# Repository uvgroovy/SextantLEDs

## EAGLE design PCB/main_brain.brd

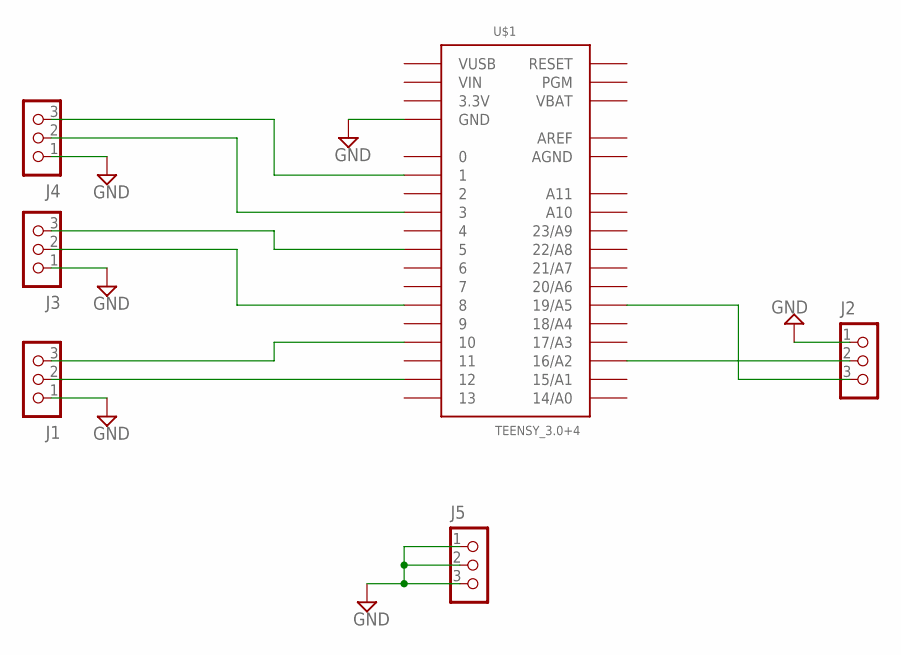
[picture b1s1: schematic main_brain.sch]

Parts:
J1, J2, J3, J4, J5: CON_TERMINAL_BLOCK_03-5MM; TERMINAL_BLOCK_3P_5
U$1: TEENSY_3.0+4

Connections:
3.3V: U$1.3.3V, U$1.3.3V1 (3.3V)
AGND: U$1.AGND
AREF: U$1.AREF
GND: J1.1, J2.1, J3.1, J4.1, J5.1, J5.2, J5.3, U$1.GND, U$1.GND1 (GND)
unnamed: J1.2, U$1.12
unnamed: J4.2, U$1.3
unnamed: J4.3, U$1.1
unnamed: J3.3, U$1.5
unnamed: J3.2, U$1.8
unnamed: J1.3, U$1.10
unnamed: J2.2, U$1.16/A2
unnamed: J2.3, U$1.19/A5
VBAT: U$1.VBAT
VIN: U$1.VIN
VUSB: U$1.VUSB

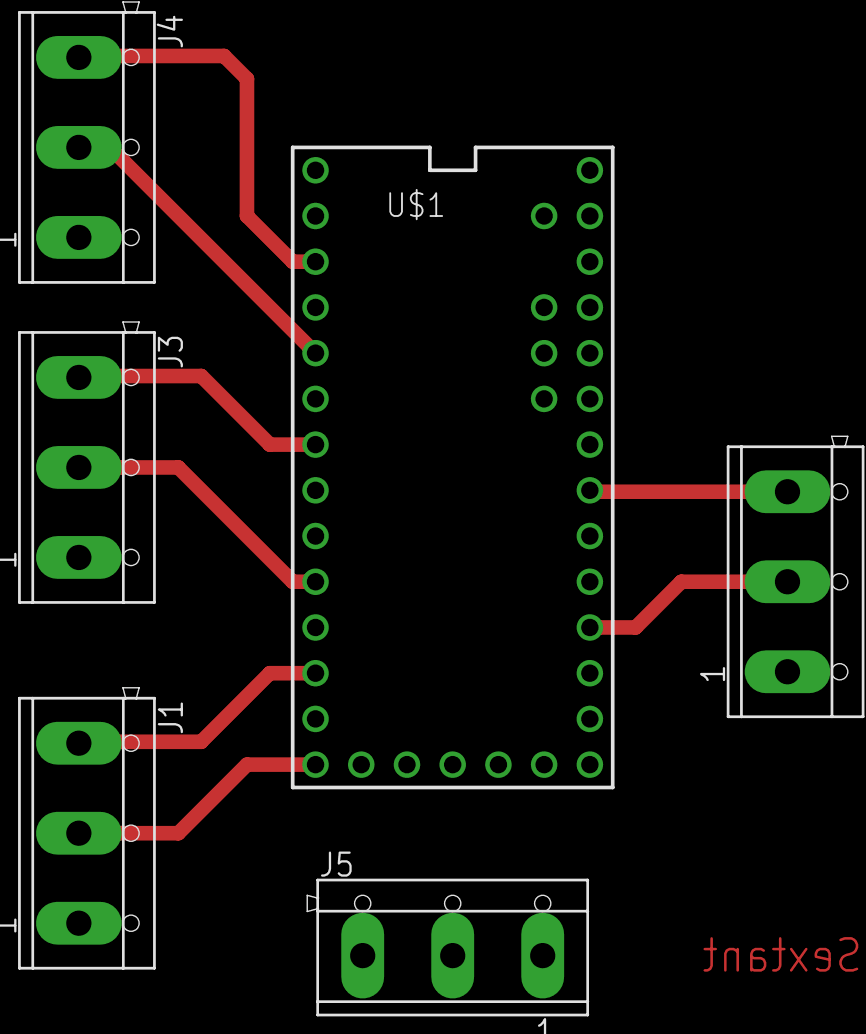
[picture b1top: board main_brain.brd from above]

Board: 2 copper layers, 6 parts (0 on the bottom side), 10 nets.

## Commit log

2015-08-20 minor
2015-08-20 added P5 demos
2015-08-20 added pixelInvaders compile
2015-08-22 adaptation of matts firmware that works better with my laptop
2015-08-22 fix serial sync issue
2015-08-22 added second party mode
2015-08-23 step-by-step pi setup instuctions
2015-08-23 in the pi the serial port shows as first
2015-08-23 re-enable fft
2015-08-23 initial commit for sign firmware
2015-08-23 more animations
2015-08-23 minors
2015-08-23 pi setup readme
2015-08-23 more setup pi docs
2015-08-23 fritzing refernce to make my life easier when soldering the prefboard
2015-08-23 update setup with wifi connection
2015-08-23 created pi folder
2015-08-23 removed debug prints from fft code
2015-08-23 changed to serial 0
2015-08-23 chagned to the right serial port on the pi
2015-08-24 gamma fix
2015-08-25 added dmx code instructions
2015-08-25 go instructions
2015-08-26 added script to run processing commands via ssh
2015-08-27 Added convo
2015-08-27 readme
2015-08-27 refresh only if button pressed
2015-08-28 added morse code convo
2015-08-28 added morse code
2015-08-29 turn led on serial
2015-08-29 small fixes
